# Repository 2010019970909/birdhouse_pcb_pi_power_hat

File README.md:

# birdhouse_pcb_pi_power_hat
birdhouse_pcb_pi_power_hat

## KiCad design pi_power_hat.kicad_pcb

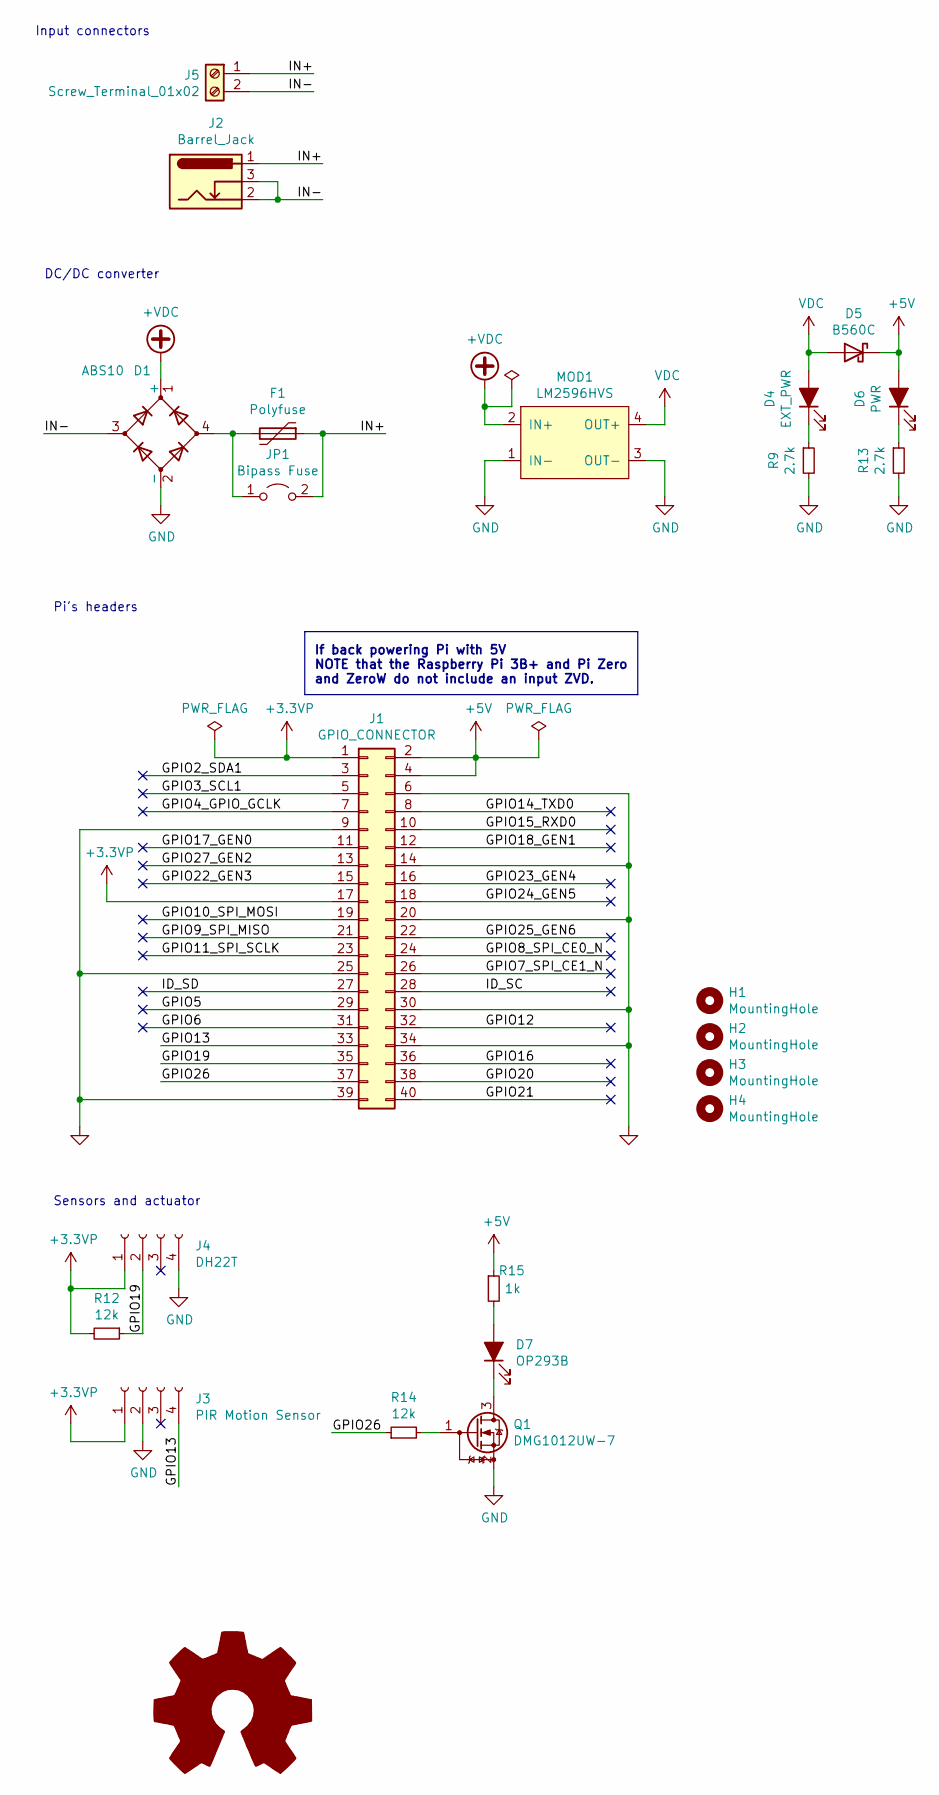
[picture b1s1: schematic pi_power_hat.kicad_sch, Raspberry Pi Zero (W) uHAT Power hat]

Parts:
D1: ABS10; Diode_Bridge_Diotec_ABS
D4: EXT_PWR; LED_0603_1608Metric
D5: B560C; D_SMC
D6: PWR; LED_0603_1608Metric
D7: OP293B; TO-46-2
F1: Polyfuse; FUSE-TH_L10.4-W3.1-P5.10-D0.8-S1.50
H1, H2, H3, H4: MountingHole; MountingHole_2.7mm_M2.5_uHAT_RPi
J1: GPIO_CONNECTOR; PinSocket_2x20_P2.54mm_Vertical_Centered_Anchor
J2: Barrel_Jack; GRAVITECH_CON-SOCJ-2155
J3: PIR Motion Sensor; PinHeader_1x04_P2.54mm_Vertical
J4: DH22T; PinHeader_1x04_P2.54mm_Vertical
J5: Screw_Terminal_01x02; CONN-TH_P5.00_KF301-5.0-2P
JP1: Bipass Fuse; SolderJumper-2_P1.3mm_Open_RoundedPad1.0x1.5mm
MOD1: LM2596HVS; Module_LM2596HVS
Q1: DMG1012UW-7; SOT-323_SC-70
R9, R13: 2.7k; R_0402_1005Metric
R12, R14: 12k; R_0402_1005Metric
R15: 1k; R_0402_1005Metric

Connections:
+3.3VP: J1.1, J1.17, J3.1, J4.1, R12.2
+5V: D5.1 (K), D6.2 (A), J1.2, J1.4, R15.1
+VDC: D1.1 (+), MOD1.2 (IN+)
/GPIO2_SDA1: J1.3
/GPIO3_SCL1: J1.5
/GPIO4_GPIO_GCLK: J1.7
/GPIO5: J1.29
/GPIO6: J1.31
/GPIO7_SPI_CE1_N: J1.26
/GPIO8_SPI_CE0_N: J1.24
/GPIO9_SPI_MISO: J1.21
/GPIO10_SPI_MOSI: J1.19
/GPIO11_SPI_SCLK: J1.23
/GPIO12: J1.32
/GPIO13: J1.33, J3.4
/GPIO14_TXD0: J1.8
/GPIO15_RXD0: J1.10
/GPIO16: J1.36
/GPIO17_GEN0: J1.11
/GPIO18_GEN1: J1.12
/GPIO19: J1.35, J4.2, R12.1
/GPIO20: J1.38
/GPIO21: J1.40
/GPIO22_GEN3: J1.15
/GPIO23_GEN4: J1.16
/GPIO24_GEN5: J1.18
/GPIO25_GEN6: J1.22
/GPIO26: J1.37, R14.1
/GPIO27_GEN2: J1.13
/ID_SC: J1.28
/ID_SD: J1.27
/IN+: F1.1, J2.1, J5.1, JP1.2 (B)
/IN-: D1.3, J2.2, J2.3, J5.2
GND: D1.2 (-), J1.6, J1.9, J1.14, J1.20, J1.25, J1.30, J1.34, J1.39, J3.2, J4.4, MOD1.1 (IN-), MOD1.3 (OUT-), Q1.2 (S), R9.2, R13.2
unnamed: D1.4, F1.2, JP1.1 (A)
unnamed: D4.1 (K), R9.1
unnamed: D6.1 (K), R13.1
unnamed: D7.1 (K), Q1.3 (D)
unnamed: D7.2 (A), R15.2
unnamed: Q1.1 (G), R14.2
VDC: D4.2 (A), D5.2 (A), MOD1.4 (OUT+)

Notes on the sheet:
Input connectors
DC/DC converter
Pi's headers
If back powering Pi with 5V NOTE that the Raspberry Pi 3B+ and Pi Zero and ZeroW do not include an input ZVD.
Sensors and actuator

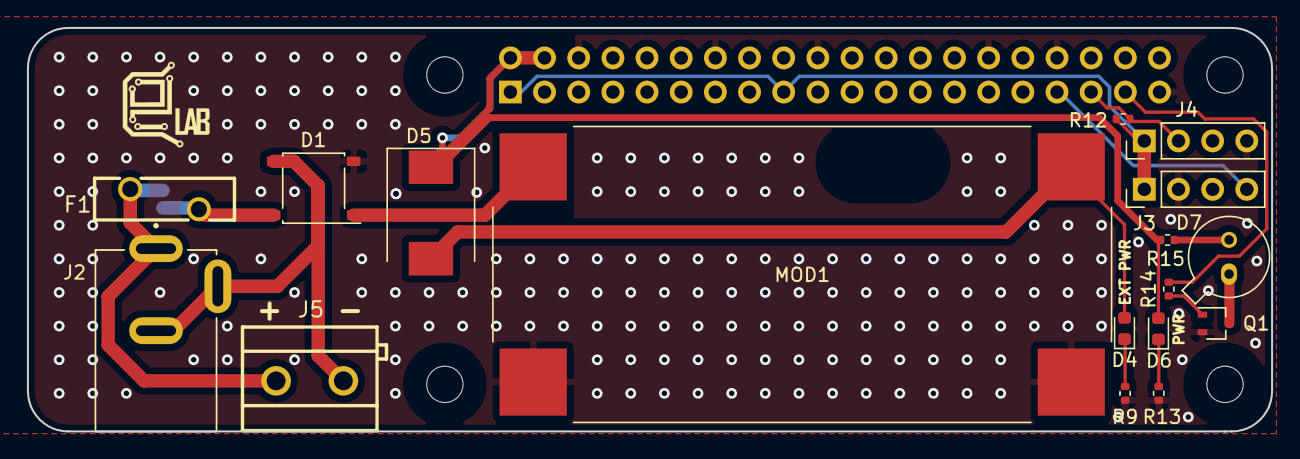
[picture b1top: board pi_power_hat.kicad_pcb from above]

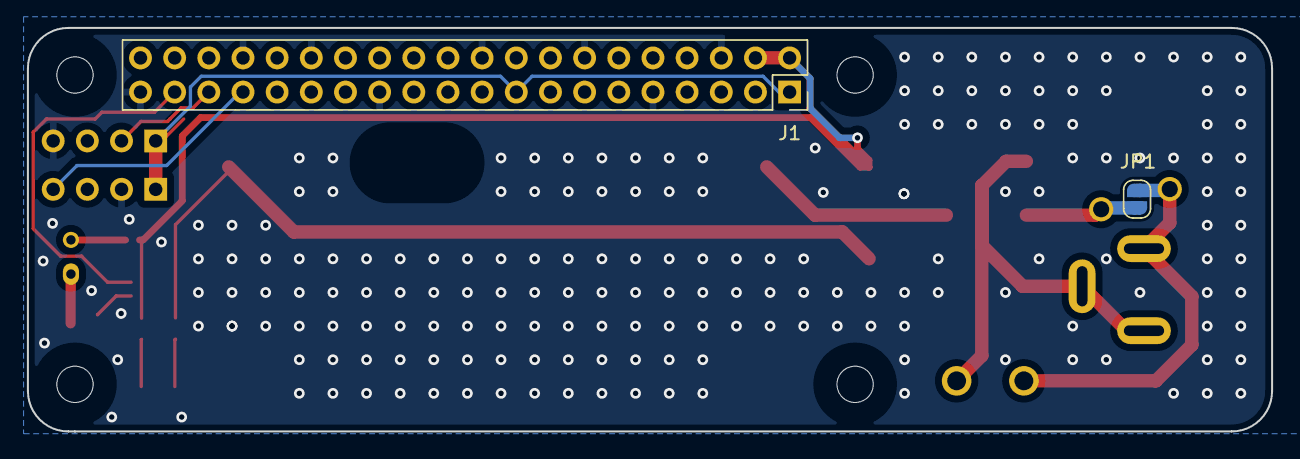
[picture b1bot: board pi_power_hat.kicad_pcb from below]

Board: 2 copper layers, 92.5 x 30.0 mm, 23 parts (2 on the bottom side), 16 nets.

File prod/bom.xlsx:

Comment | Designator | Footprint | LCSC Part Number
2.7 kOhms | R9, R13 | 0402 | C415168
12 kOhms | R12, R14 | 0402 | C363271
1 kOhms | R15 | 0402 | C283960
ABS10 | D1 | ABS | C190798
LED (orange) | D4,D6 | 0603 | C401116
DMG1012UW-7 | Q1 | SOT-323(SC-70) | C156390
B560C | D5 | SMC(DO-214AB) | C85100
Polyfuse | F1 | TH_L10.4… | C135427 ??? (je ne sais plus, c'est le dernier mentioné sur Discord)
Pi Header | J1 |  | C35165
Barrel Jack | J2 |  | https://www.mouser.be/ProductDetail/Gravitech/CON-SOCJ-2155?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
Sensors | J3, J4 |  | C124378
Screw terminal | J5 |  | C474881
LM2596HVS | MOD1 |  | https://www.amazon.fr/gp/product/B00U6Y9YPM/ref=ppx_yo_dt_b_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

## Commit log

2021-12-20 Create a new power hat.
2021-12-20 Add input connectors
2021-12-24 Add fuse
2022-01-16 Change in design

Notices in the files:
pi_power_hat.kicad_pcb:
This PCB design is licensed under MIT Open Source License.
pi_power_hat.kicad_sch:
This Schematic is licensed under MIT Open Source License.
